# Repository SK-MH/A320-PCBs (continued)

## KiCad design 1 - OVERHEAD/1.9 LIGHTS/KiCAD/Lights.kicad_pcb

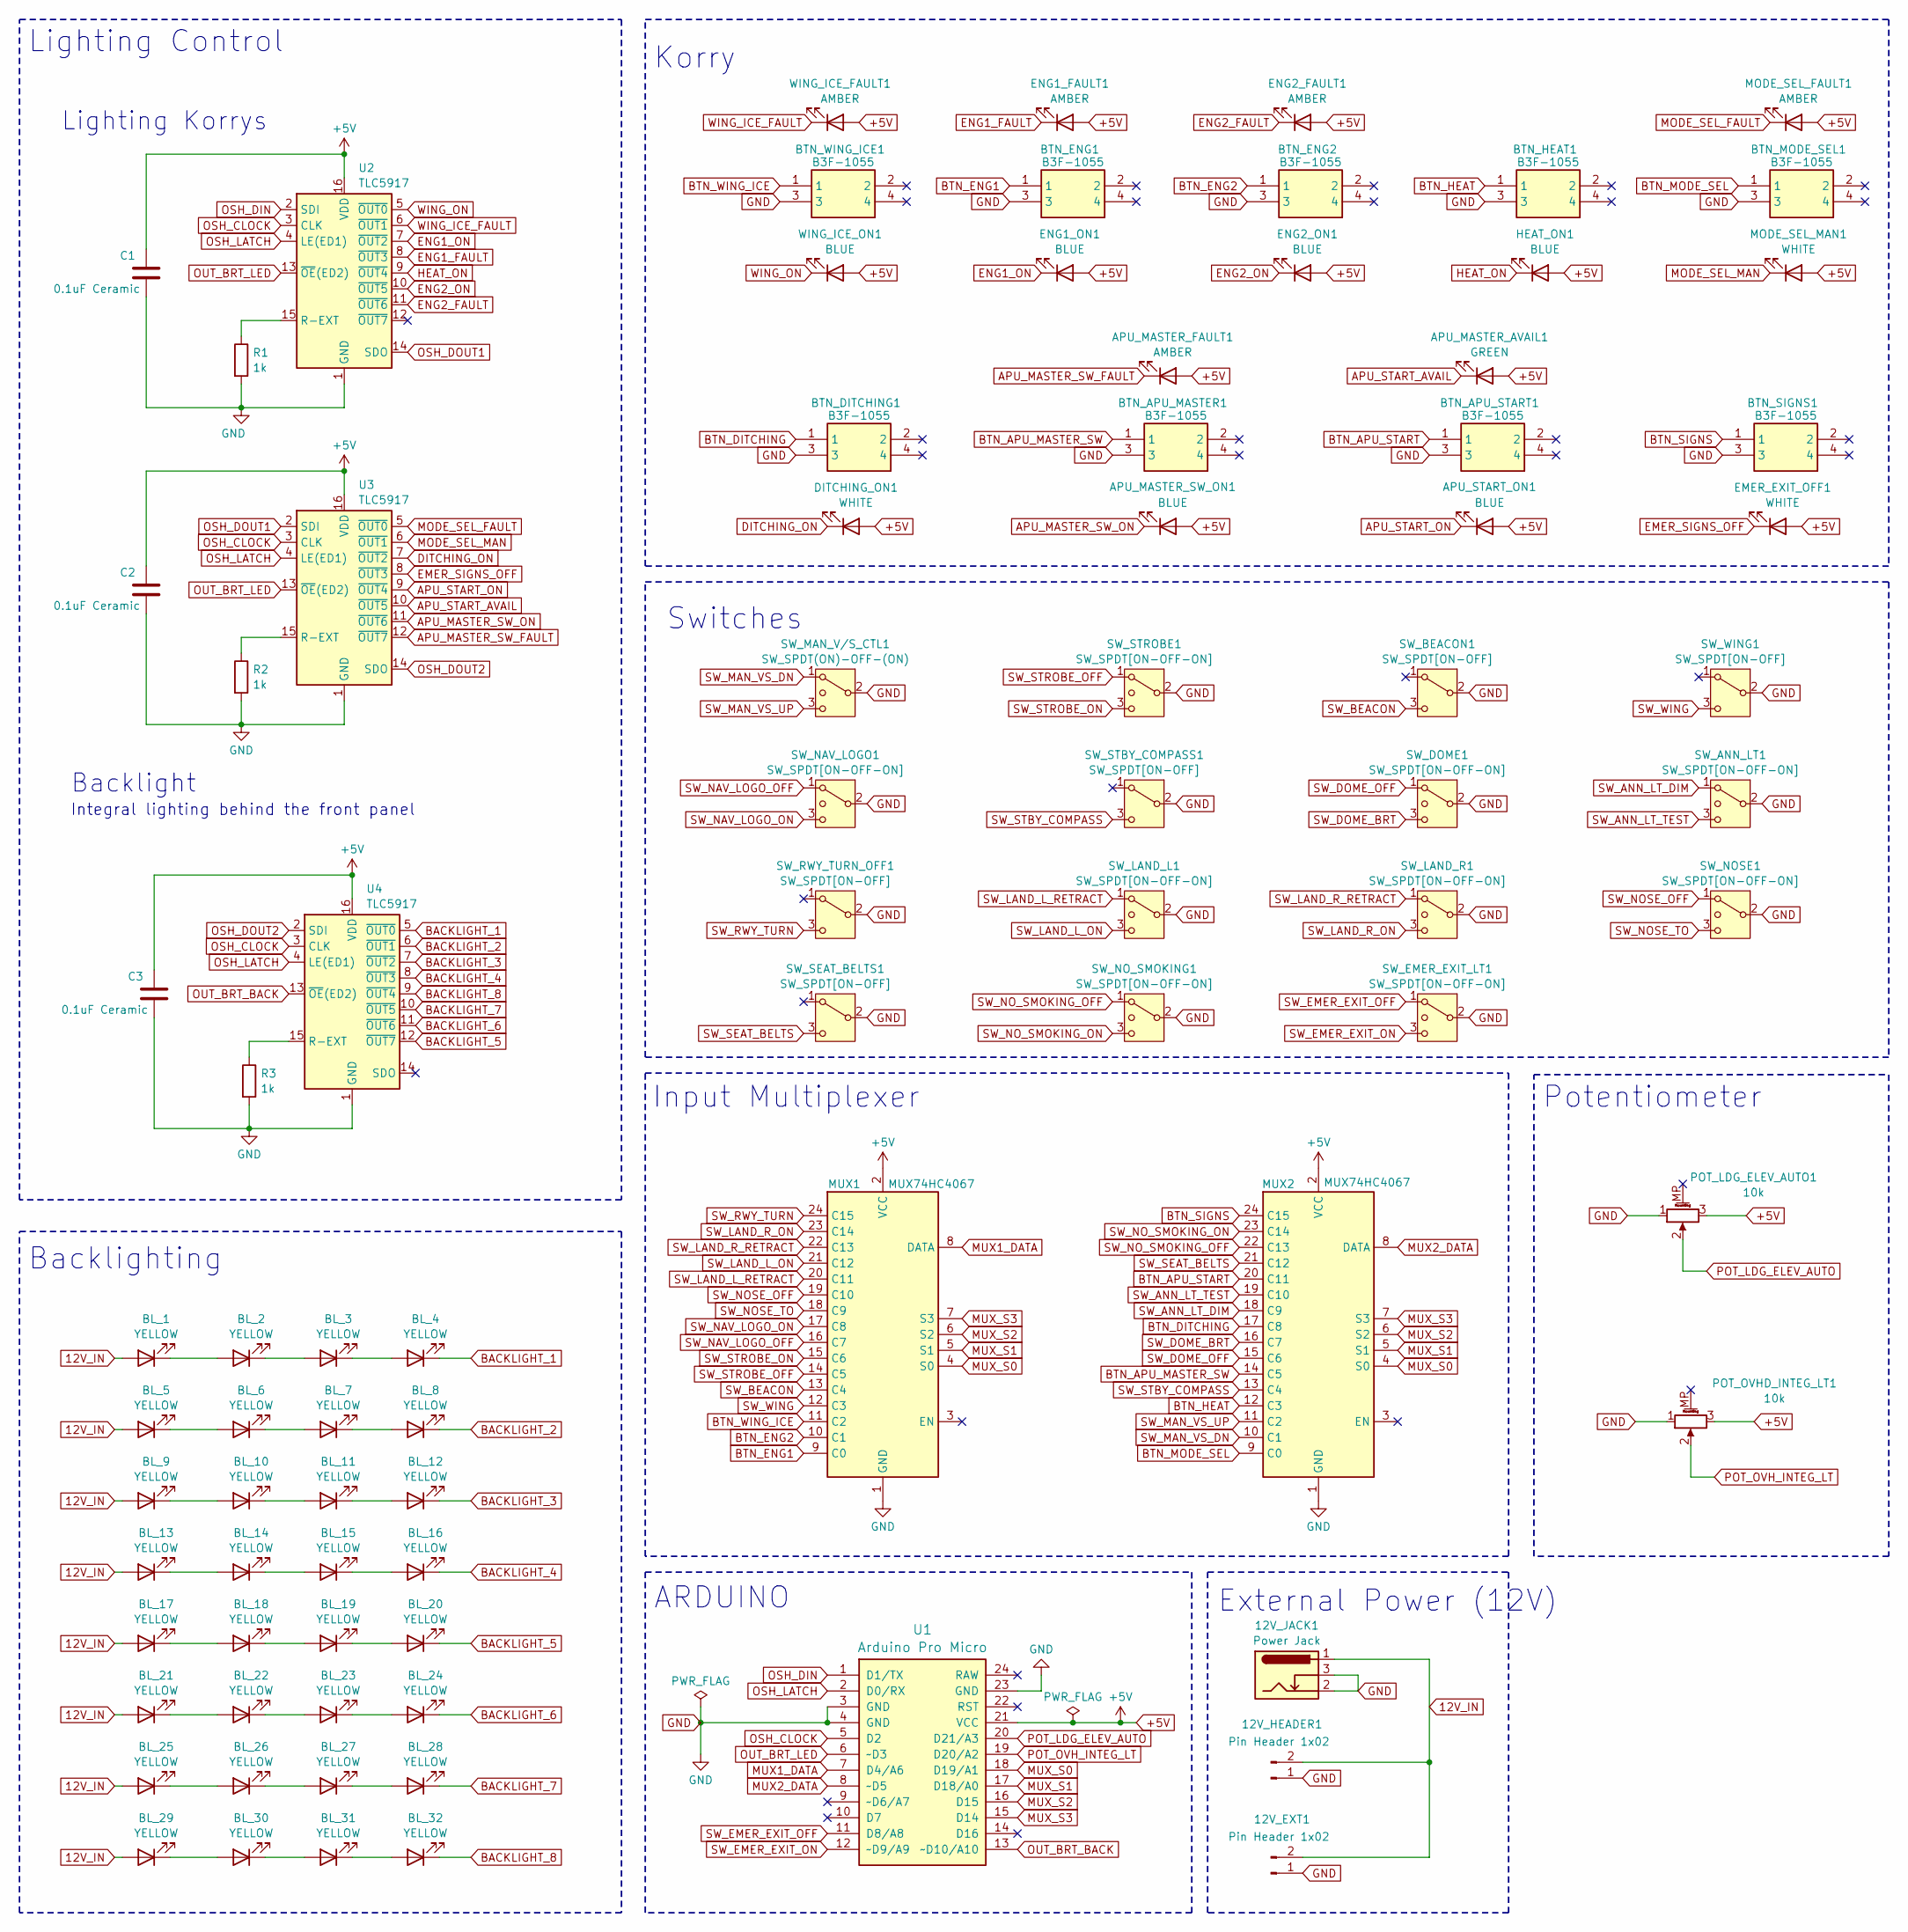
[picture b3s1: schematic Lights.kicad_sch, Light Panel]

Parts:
12V_EXT1, 12V_HEADER1: Pin Header 1x02; JST_EH_B2B-EH-A_1x02_P2.50mm_Vertical
12V_JACK1: Power Jack; BarrelJack_Horizontal
APU_MASTER_AVAIL1: GREEN; LED_D3.0mm
APU_MASTER_FAULT1: AMBER; LED_D3.0mm
APU_MASTER_SW_ON1: BLUE; LED_D3.0mm
APU_START_ON1: BLUE; LED_D3.0mm
BL_1, BL_2, BL_3, BL_4, BL_5, BL_6, BL_7, BL_8, BL_9, BL_10, BL_11, BL_12, BL_13, BL_14, BL_15, BL_16, BL_17, BL_18, BL_19, BL_20, BL_21, BL_22, BL_23, BL_24, BL_25, BL_26, BL_27, BL_28, BL_29, BL_30, BL_31, BL_32: YELLOW; LED_D3.0mm
BTN_APU_MASTER1: B3F-1055; B3F1000; Mouser Part Number 653-B3F-1055
BTN_APU_START1: B3F-1055; B3F1000; Mouser Part Number 653-B3F-1055
BTN_DITCHING1: B3F-1055; B3F1000; Mouser Part Number 653-B3F-1055
BTN_ENG1, BTN_ENG2: B3F-1055; B3F1000; Mouser Part Number 653-B3F-1055
BTN_HEAT1: B3F-1055; B3F1000; Mouser Part Number 653-B3F-1055
BTN_MODE_SEL1: B3F-1055; B3F1000; Mouser Part Number 653-B3F-1055
BTN_SIGNS1: B3F-1055; B3F1000; Mouser Part Number 653-B3F-1055
BTN_WING_ICE1: B3F-1055; B3F1000; Mouser Part Number 653-B3F-1055
C1, C2, C3: 0.1uF Ceramic; C_Disc_D3.0mm_W1.6mm_P2.50mm
DITCHING_ON1: WHITE; LED_D3.0mm
EMER_EXIT_OFF1: WHITE; LED_D3.0mm
ENG1_FAULT1, ENG2_FAULT1: AMBER; LED_D3.0mm
ENG1_ON1, ENG2_ON1: BLUE; LED_D3.0mm
HEAT_ON1: BLUE; LED_D3.0mm
MODE_SEL_FAULT1: AMBER; LED_D3.0mm
MODE_SEL_MAN1: WHITE; LED_D3.0mm
MUX1, MUX2: MUX74HC4067
POT_LDG_ELEV_AUTO1: 10k; Potentiometer_Alps_RK09K_Single_Vertical
POT_OVHD_INTEG_LT1: 10k; Potentiometer_Alps_RK09K_Single_Vertical
R1, R2, R3: 1k; R_Axial_DIN0204_L3.6mm_D1.6mm_P5.08mm_Horizontal
SW_ANN_LT1: SW_SPDT[ON-OFF-ON]; T80-Z1
SW_BEACON1: SW_SPDT[ON-OFF]; T80-Z1
SW_DOME1: SW_SPDT[ON-OFF-ON]; T80-Z1
SW_EMER_EXIT_LT1: SW_SPDT[ON-OFF-ON]; T80-Z1
SW_LAND_L1: SW_SPDT[ON-OFF-ON]; T80-Z1
SW_LAND_R1: SW_SPDT[ON-OFF-ON]; T80-Z1
SW_MAN_V/S_CTL1: SW_SPDT(ON)-OFF-(ON); T80-Z1
SW_NAV_LOGO1: SW_SPDT[ON-OFF-ON]; T80-Z1
SW_NOSE1: SW_SPDT[ON-OFF-ON]; T80-Z1
SW_NO_SMOKING1: SW_SPDT[ON-OFF-ON]; T80-Z1
SW_RWY_TURN_OFF1: SW_SPDT[ON-OFF]; T80-Z1
SW_SEAT_BELTS1: SW_SPDT[ON-OFF]; T80-Z1
SW_STBY_COMPASS1: SW_SPDT[ON-OFF]; T80-Z1
SW_STROBE1: SW_SPDT[ON-OFF-ON]; T80-Z1
SW_WING1: SW_SPDT[ON-OFF]; T80-Z1
U1: Arduino Pro Micro; Sparkfun_Pro_Micro
U2, U3, U4: TLC5917; DIP-16_W7.62mm
WING_ICE_FAULT1: AMBER; LED_D3.0mm
WING_ICE_ON1: BLUE; LED_D3.0mm

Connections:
12V_IN: 12V_EXT1.2, 12V_HEADER1.2, 12V_JACK1.1, BL_1.2 (A), BL_5.2 (A), BL_9.2 (A), BL_13.2 (A), BL_17.2 (A), BL_21.2 (A), BL_25.2 (A), BL_29.2 (A)
+5V: APU_MASTER_AVAIL1.2 (A), APU_MASTER_FAULT1.2 (A), APU_MASTER_SW_ON1.2 (A), APU_START_ON1.2 (A), C1.1, C2.1, C3.1, DITCHING_ON1.2 (A), EMER_EXIT_OFF1.2 (A), ENG1_FAULT1.2 (A), ENG1_ON1.2 (A), ENG2_FAULT1.2 (A), ENG2_ON1.2 (A), HEAT_ON1.2 (A), MODE_SEL_FAULT1.2 (A), MODE_SEL_MAN1.2 (A), MUX1.2 (VCC), MUX2.2 (VCC), POT_LDG_ELEV_AUTO1.3, POT_OVHD_INTEG_LT1.3, U1.21 (VCC), U2.16 (VDD), U3.16 (VDD), U4.16 (VDD), WING_ICE_FAULT1.2 (A), WING_ICE_ON1.2 (A)
APU_MASTER_SW_FAULT: APU_MASTER_FAULT1.1 (K), U3.12 (~OUT7)
APU_MASTER_SW_ON: APU_MASTER_SW_ON1.1 (K), U3.11 (~OUT6)
APU_START_AVAIL: APU_MASTER_AVAIL1.1 (K), U3.10 (~OUT5)
APU_START_ON: APU_START_ON1.1 (K), U3.9 (~OUT4)
BACKLIGHT_1: BL_4.1 (K), U4.5 (~OUT0)
BACKLIGHT_2: BL_8.1 (K), U4.6 (~OUT1)
BACKLIGHT_3: BL_12.1 (K), U4.7 (~OUT2)
BACKLIGHT_4: BL_16.1 (K), U4.8 (~OUT3)
BACKLIGHT_5: BL_20.1 (K), U4.12 (~OUT7)
BACKLIGHT_6: BL_24.1 (K), U4.11 (~OUT6)
BACKLIGHT_7: BL_28.1 (K), U4.10 (~OUT5)
BACKLIGHT_8: BL_32.1 (K), U4.9 (~OUT4)
BTN_APU_MASTER_SW: BTN_APU_MASTER1.1, MUX2.14 (C5)
BTN_APU_START: BTN_APU_START1.1, MUX2.20 (C11)
BTN_DITCHING: BTN_DITCHING1.1, MUX2.17 (C8)
BTN_ENG1: BTN_ENG1.1, MUX1.9 (C0)
BTN_ENG2: BTN_ENG2.1, MUX1.10 (C1)
BTN_HEAT: BTN_HEAT1.1, MUX2.12 (C3)
BTN_MODE_SEL: BTN_MODE_SEL1.1, MUX2.9 (C0)
BTN_SIGNS: BTN_SIGNS1.1, MUX2.24 (C15)
BTN_WING_ICE: BTN_WING_ICE1.1, MUX1.11 (C2)
DITCHING_ON: DITCHING_ON1.1 (K), U3.7 (~OUT2)
EMER_SIGNS_OFF: EMER_EXIT_OFF1.1 (K), U3.8 (~OUT3)
ENG1_FAULT: ENG1_FAULT1.1 (K), U2.8 (~OUT3)
ENG1_ON: ENG1_ON1.1 (K), U2.7 (~OUT2)
ENG2_FAULT: ENG2_FAULT1.1 (K), U2.11 (~OUT6)
ENG2_ON: ENG2_ON1.1 (K), U2.10 (~OUT5)
GND: 12V_EXT1.1, 12V_HEADER1.1, 12V_JACK1.2, 12V_JACK1.3, BTN_APU_MASTER1.3, BTN_APU_START1.3, BTN_DITCHING1.3, BTN_ENG1.3, BTN_ENG2.3, BTN_HEAT1.3, BTN_MODE_SEL1.3, BTN_SIGNS1.3, BTN_WING_ICE1.3, C1.2, C2.2, C3.2, MUX1.1 (GND), MUX2.1 (GND), POT_LDG_ELEV_AUTO1.1, POT_OVHD_INTEG_LT1.1, R1.2, R2.2, R3.2, SW_ANN_LT1.2 (3), SW_BEACON1.2 (B), SW_DOME1.2 (3), SW_EMER_EXIT_LT1.2 (3), SW_LAND_L1.2 (3), SW_LAND_R1.2 (3), SW_MAN_V/S_CTL1.2 (3), SW_NAV_LOGO1.2 (3), SW_NOSE1.2 (3), SW_NO_SMOKING1.2 (3), SW_RWY_TURN_OFF1.2 (B), SW_SEAT_BELTS1.2 (B), SW_STBY_COMPASS1.2 (B), SW_STROBE1.2 (3), SW_WING1.2 (B), U1.3 (GND), U1.4 (GND), U1.23 (GND), U2.1 (GND), U3.1 (GND), U4.1 (GND)
HEAT_ON: HEAT_ON1.1 (K), U2.9 (~OUT4)
MODE_SEL_FAULT: MODE_SEL_FAULT1.1 (K), U3.5 (~OUT0)
MODE_SEL_MAN: MODE_SEL_MAN1.1 (K), U3.6 (~OUT1)
MUX1_DATA: MUX1.8 (DATA), U1.7 (D4/A6)
MUX2_DATA: MUX2.8 (DATA), U1.8 (~D5)
MUX_S0: MUX1.4 (S0), MUX2.4 (S0), U1.18 (D19/A1)
MUX_S1: MUX1.5 (S1), MUX2.5 (S1), U1.17 (D18/A0)
MUX_S2: MUX1.6 (S2), MUX2.6 (S2), U1.16 (D15)
MUX_S3: MUX1.7 (S3), MUX2.7 (S3), U1.15 (D14)
unnamed: BL_1.1 (K), BL_2.2 (A)
unnamed: BL_2.1 (K), BL_3.2 (A)
unnamed: BL_3.1 (K), BL_4.2 (A)
unnamed: BL_5.1 (K), BL_6.2 (A)
unnamed: BL_6.1 (K), BL_7.2 (A)
unnamed: BL_7.1 (K), BL_8.2 (A)
unnamed: BL_9.1 (K), BL_10.2 (A)
unnamed: BL_10.1 (K), BL_11.2 (A)
unnamed: BL_11.1 (K), BL_12.2 (A)
unnamed: BL_13.1 (K), BL_14.2 (A)
unnamed: BL_14.1 (K), BL_15.2 (A)
unnamed: BL_15.1 (K), BL_16.2 (A)
unnamed: BL_17.1 (K), BL_18.2 (A)
unnamed: BL_18.1 (K), BL_19.2 (A)
unnamed: BL_19.1 (K), BL_20.2 (A)
unnamed: BL_21.1 (K), BL_22.2 (A)
unnamed: BL_22.1 (K), BL_23.2 (A)
unnamed: BL_23.1 (K), BL_24.2 (A)
unnamed: BL_25.1 (K), BL_26.2 (A)
unnamed: BL_26.1 (K), BL_27.2 (A)
unnamed: BL_27.1 (K), BL_28.2 (A)
unnamed: BL_29.1 (K), BL_30.2 (A)
unnamed: BL_30.1 (K), BL_31.2 (A)
unnamed: BL_31.1 (K), BL_32.2 (A)
unnamed: R1.1, U2.15 (R-EXT)
unnamed: R2.1, U3.15 (R-EXT)
unnamed: R3.1, U4.15 (R-EXT)
OSH_CLOCK: U1.5 (D2), U2.3 (CLK), U3.3 (CLK), U4.3 (CLK)
OSH_DIN: U1.1 (D1/TX), U2.2 (SDI)
OSH_DOUT1: U2.14 (SDO), U3.2 (SDI)
OSH_DOUT2: U3.14 (SDO), U4.2 (SDI)
OSH_LATCH: U1.2 (D0/RX), U2.4 (LE(ED1)), U3.4 (LE(ED1)), U4.4 (LE(ED1))
OUT_BRT_BACK: U1.13 (~D10/A10), U4.13 (~OE(ED2))
OUT_BRT_LED: U1.6 (~D3), U2.13 (~OE(ED2)), U3.13 (~OE(ED2))
POT_LDG_ELEV_AUTO: POT_LDG_ELEV_AUTO1.2, U1.20 (D21/A3)
POT_OVH_INTEG_LT: POT_OVHD_INTEG_LT1.2, U1.19 (D20/A2)
SW_ANN_LT_DIM: MUX2.18 (C9), SW_ANN_LT1.1
SW_ANN_LT_TEST: MUX2.19 (C10), SW_ANN_LT1.3 (4)
SW_BEACON: MUX1.13 (C4), SW_BEACON1.3 (C)
SW_DOME_BRT: MUX2.16 (C7), SW_DOME1.3 (4)
SW_DOME_OFF: MUX2.15 (C6), SW_DOME1.1
SW_EMER_EXIT_OFF: SW_EMER_EXIT_LT1.1, U1.11 (D8/A8)
SW_EMER_EXIT_ON: SW_EMER_EXIT_LT1.3 (4), U1.12 (~D9/A9)
SW_LAND_L_ON: MUX1.21 (C12), SW_LAND_L1.3 (4)
SW_LAND_L_RETRACT: MUX1.20 (C11), SW_LAND_L1.1
SW_LAND_R_ON: MUX1.23 (C14), SW_LAND_R1.3 (4)
SW_LAND_R_RETRACT: MUX1.22 (C13), SW_LAND_R1.1
SW_MAN_VS_DN: MUX2.10 (C1), SW_MAN_V/S_CTL1.1
SW_MAN_VS_UP: MUX2.11 (C2), SW_MAN_V/S_CTL1.3 (4)
SW_NAV_LOGO_OFF: MUX1.16 (C7), SW_NAV_LOGO1.1
SW_NAV_LOGO_ON: MUX1.17 (C8), SW_NAV_LOGO1.3 (4)
SW_NOSE_OFF: MUX1.19 (C10), SW_NOSE1.1
SW_NOSE_TO: MUX1.18 (C9), SW_NOSE1.3 (4)
SW_NO_SMOKING_OFF: MUX2.22 (C13), SW_NO_SMOKING1.1
SW_NO_SMOKING_ON: MUX2.23 (C14), SW_NO_SMOKING1.3 (4)
SW_RWY_TURN: MUX1.24 (C15), SW_RWY_TURN_OFF1.3 (C)
SW_SEAT_BELTS: MUX2.21 (C12), SW_SEAT_BELTS1.3 (C)
SW_STBY_COMPASS: MUX2.13 (C4), SW_STBY_COMPASS1.3 (C)
SW_STROBE_OFF: MUX1.14 (C5), SW_STROBE1.1
SW_STROBE_ON: MUX1.15 (C6), SW_STROBE1.3 (4)
SW_WING: MUX1.12 (C3), SW_WING1.3 (C)
WING_ICE_FAULT: U2.6 (~OUT1), WING_ICE_FAULT1.1 (K)
WING_ON: U2.5 (~OUT0), WING_ICE_ON1.1 (K)

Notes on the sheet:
Backlighting
ARDUINO
Switches
Korry
Potentiometer
Input Multiplexer
External Power (12V)
Lighting Korrys
Lighting Control
Integral lighting behind the front panel
Backlight

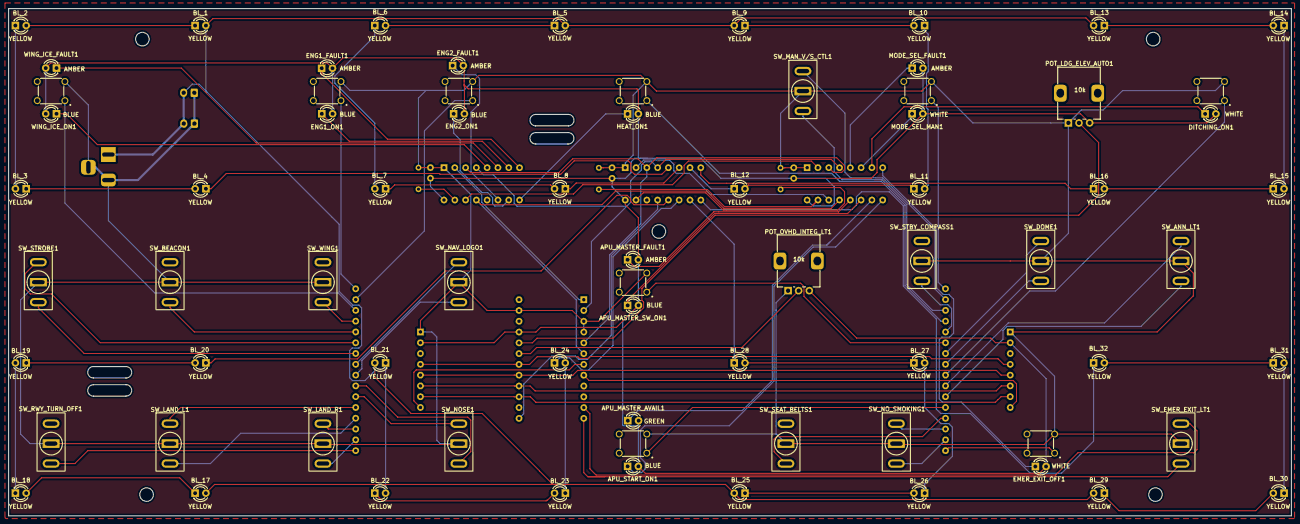
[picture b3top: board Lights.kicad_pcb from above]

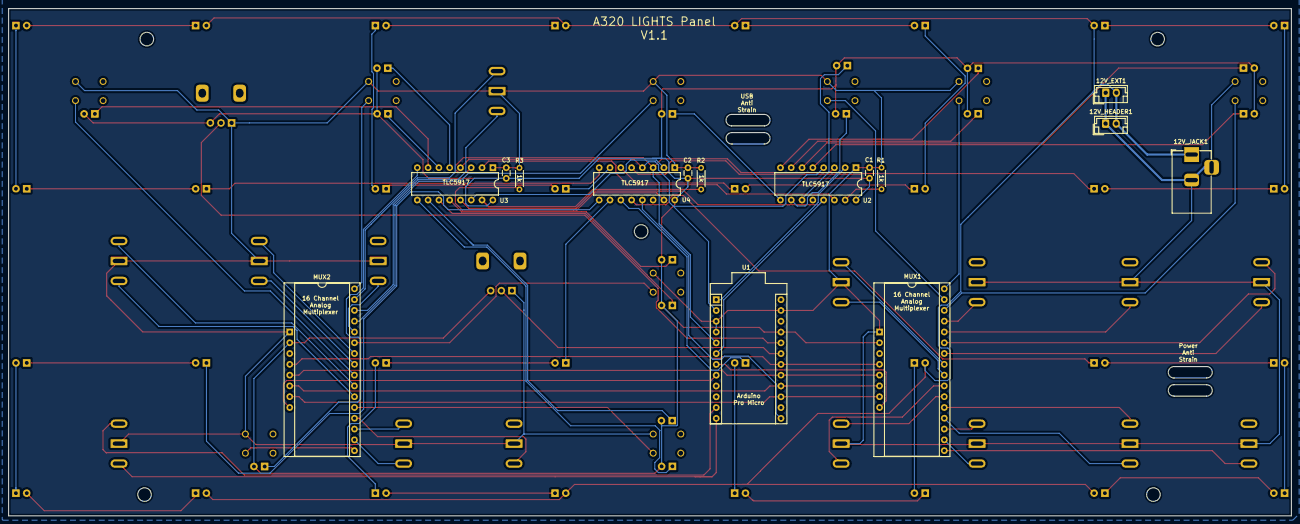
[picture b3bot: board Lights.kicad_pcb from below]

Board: 2 copper layers, 302.0 x 119.4 mm, 88 parts (15 on the bottom side), 102 nets.

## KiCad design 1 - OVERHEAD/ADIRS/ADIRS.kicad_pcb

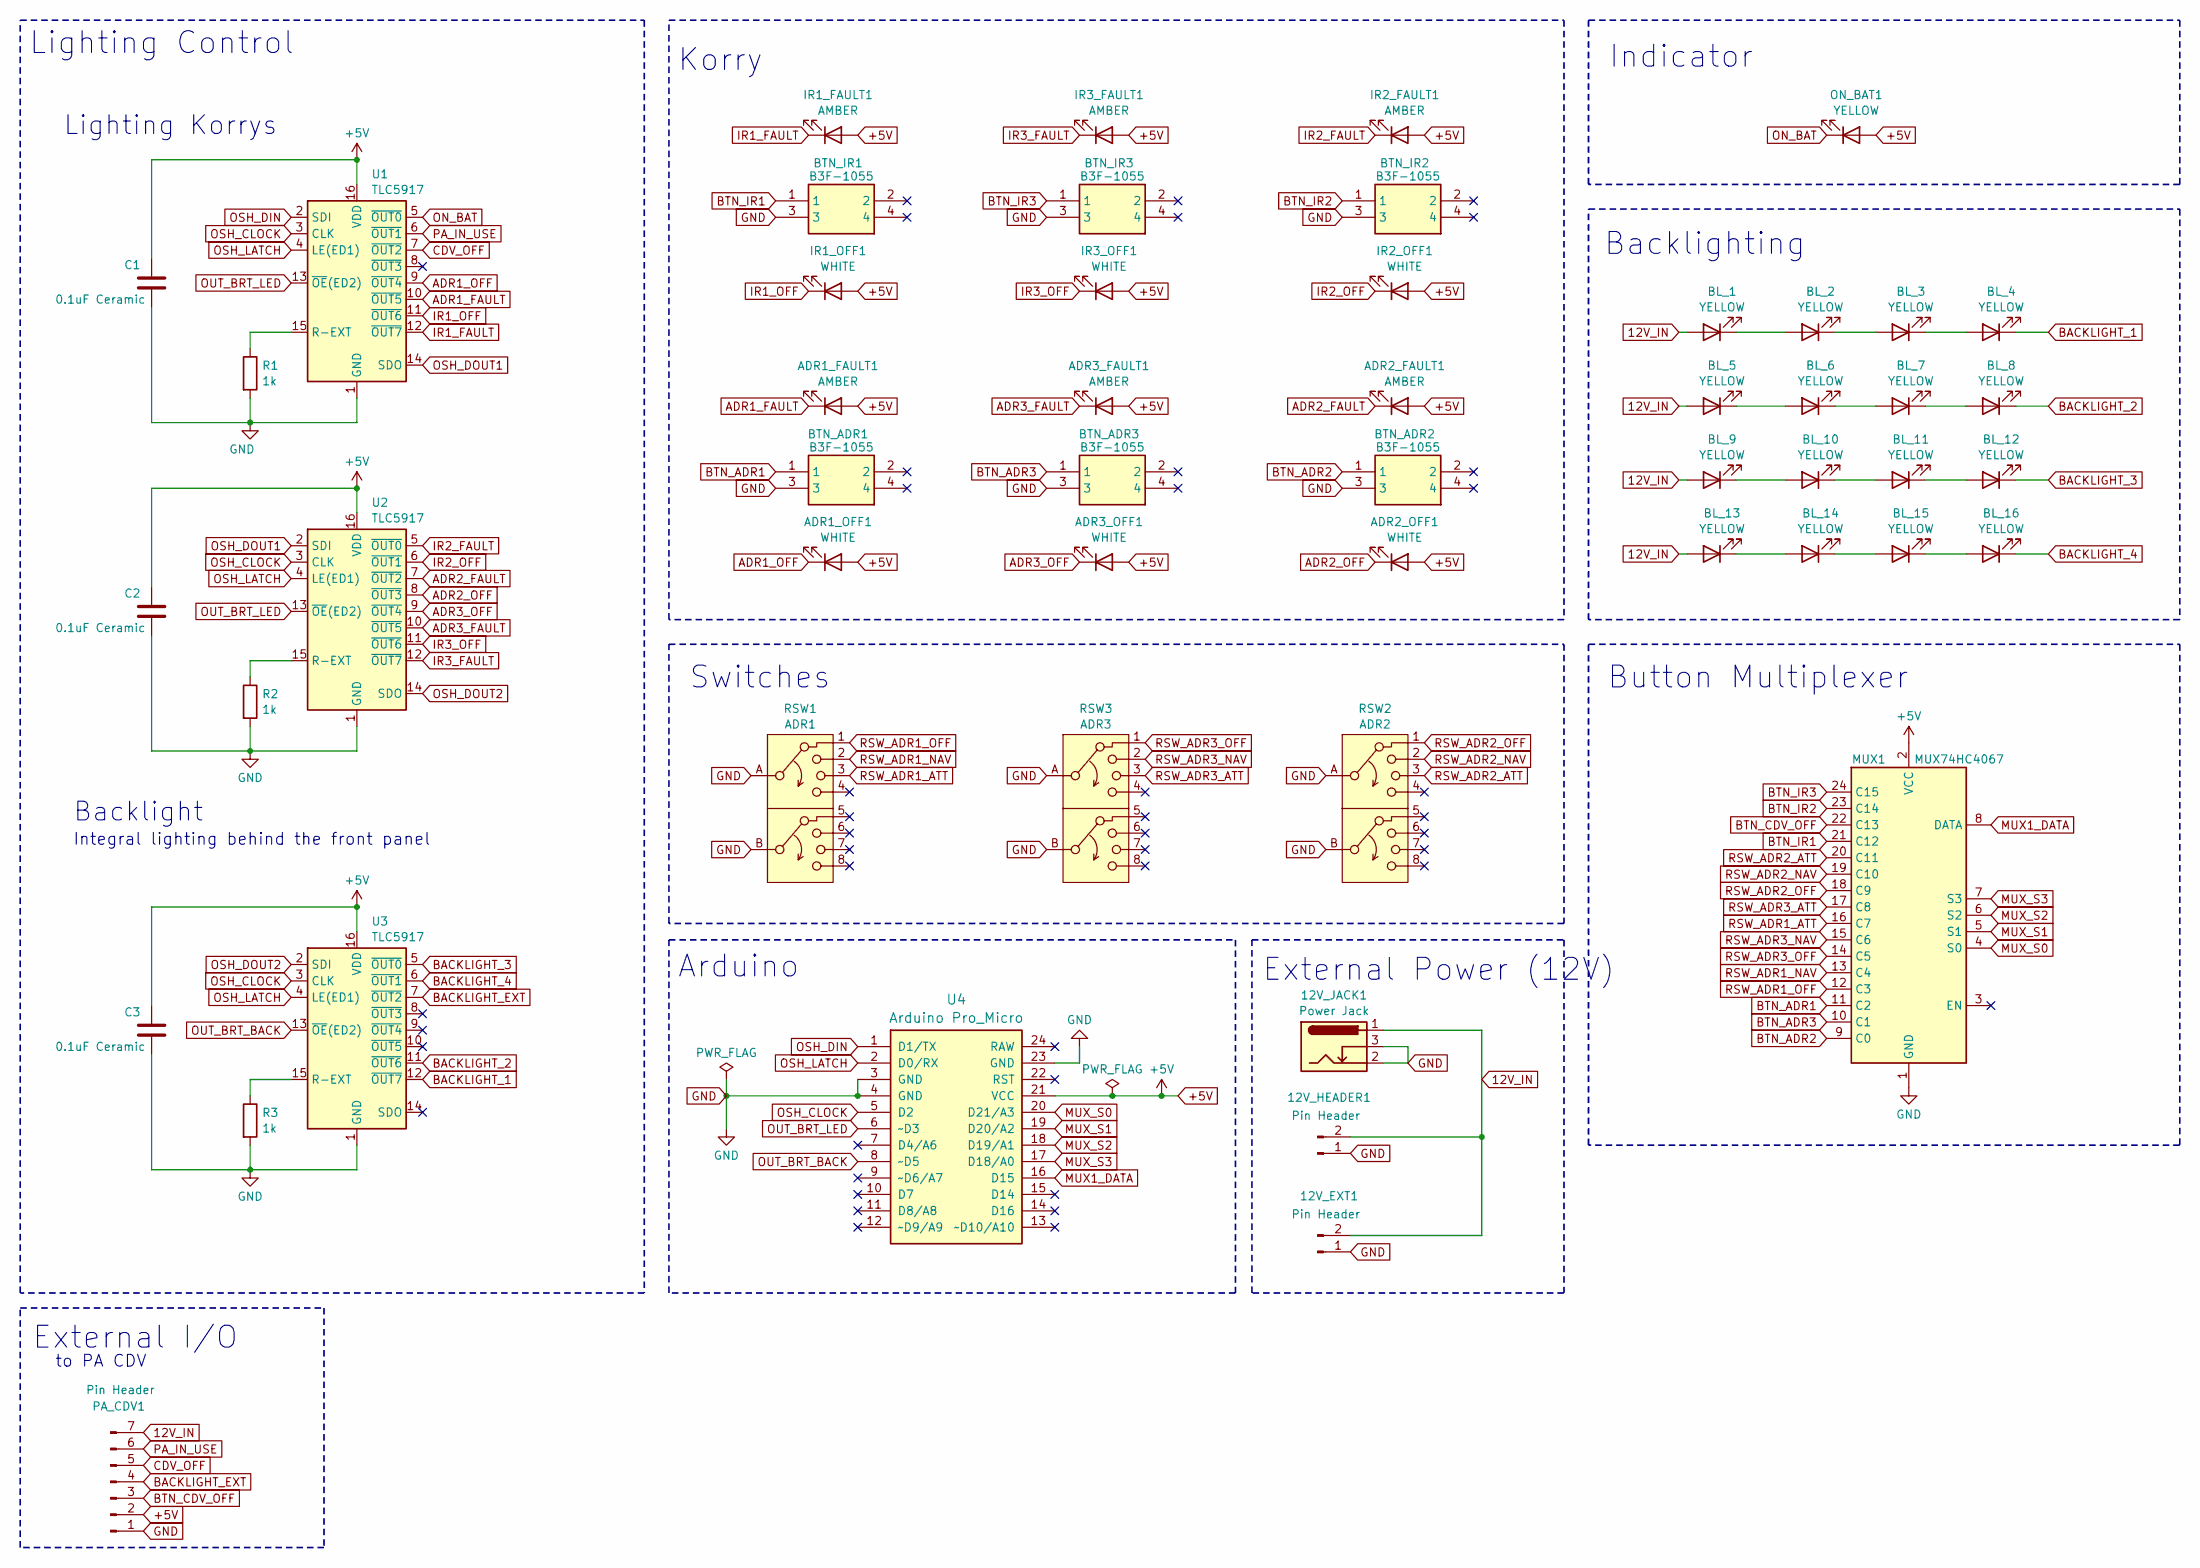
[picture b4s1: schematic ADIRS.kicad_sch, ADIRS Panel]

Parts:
12V_EXT1, 12V_HEADER1: Pin Header; JST_EH_B2B-EH-A_1x02_P2.50mm_Vertical
12V_JACK1: Power Jack; BarrelJack_Horizontal
ADR1_FAULT1, ADR2_FAULT1, ADR3_FAULT1: AMBER; LED_D3.0mm
ADR1_OFF1, ADR2_OFF1, ADR3_OFF1: WHITE; LED_D3.0mm
BL_1, BL_2, BL_3, BL_4, BL_5, BL_6, BL_7, BL_8, BL_9, BL_10, BL_11, BL_12, BL_13, BL_14, BL_15, BL_16: YELLOW; LED_D3.0mm
BTN_ADR1, BTN_ADR2, BTN_ADR3: B3F-1055; B3F1000; Mouser Part Number 653-B3F-1055
BTN_IR1, BTN_IR2, BTN_IR3: B3F-1055; B3F1000; Mouser Part Number 653-B3F-1055
C1, C2, C3: 0.1uF Ceramic; C_Disc_D3.0mm_W1.6mm_P2.50mm
IR1_FAULT1, IR2_FAULT1, IR3_FAULT1: AMBER; LED_D3.0mm
IR1_OFF1, IR2_OFF1, IR3_OFF1: WHITE; LED_D3.0mm
MUX1: MUX74HC4067
ON_BAT1: YELLOW; LED_D3.0mm
PA_CDV1: Pin Header; JST_EH_B7B-EH-A_1x07_P2.50mm_Vertical
R1, R2, R3: 1k; R_Axial_DIN0204_L3.6mm_D1.6mm_P7.62mm_Horizontal
RSW1: ADR1; SR16-AB
RSW2: ADR2; SR16-AB
RSW3: ADR3; SR16-AB
U1, U2, U3: TLC5917; DIP-16_W7.62mm
U4: Arduino Pro_Micro; Sparkfun_Pro_Micro

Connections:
12V_IN: 12V_EXT1.2, 12V_HEADER1.2, 12V_JACK1.1, BL_1.2 (A), BL_5.2 (A), BL_9.2 (A), BL_13.2 (A), PA_CDV1.7
+5V: ADR1_FAULT1.2 (A), ADR1_OFF1.2 (A), ADR2_FAULT1.2 (A), ADR2_OFF1.2 (A), ADR3_FAULT1.2 (A), ADR3_OFF1.2 (A), C1.1, C2.1, C3.1, IR1_FAULT1.2 (A), IR1_OFF1.2 (A), IR2_FAULT1.2 (A), IR2_OFF1.2 (A), IR3_FAULT1.2 (A), IR3_OFF1.2 (A), MUX1.2 (VCC), ON_BAT1.2 (A), PA_CDV1.2, U1.16 (VDD), U2.16 (VDD), U3.16 (VDD), U4.21 (VCC)
ADR1_FAULT: ADR1_FAULT1.1 (K), U1.10 (~OUT5)
ADR1_OFF: ADR1_OFF1.1 (K), U1.9 (~OUT4)
ADR2_FAULT: ADR2_FAULT1.1 (K), U2.7 (~OUT2)
ADR2_OFF: ADR2_OFF1.1 (K), U2.8 (~OUT3)
ADR3_FAULT: ADR3_FAULT1.1 (K), U2.10 (~OUT5)
ADR3_OFF: ADR3_OFF1.1 (K), U2.9 (~OUT4)
BACKLIGHT_1: BL_4.1 (K), U3.12 (~OUT7)
BACKLIGHT_2: BL_8.1 (K), U3.11 (~OUT6)
BACKLIGHT_3: BL_12.1 (K), U3.5 (~OUT0)
BACKLIGHT_4: BL_16.1 (K), U3.6 (~OUT1)
BACKLIGHT_EXT: PA_CDV1.4, U3.7 (~OUT2)
BTN_ADR1: BTN_ADR1.1, MUX1.11 (C2)
BTN_ADR2: BTN_ADR2.1, MUX1.9 (C0)
BTN_ADR3: BTN_ADR3.1, MUX1.10 (C1)
BTN_CDV_OFF: MUX1.22 (C13), PA_CDV1.3
BTN_IR1: BTN_IR1.1, MUX1.21 (C12)
BTN_IR2: BTN_IR2.1, MUX1.23 (C14)
BTN_IR3: BTN_IR3.1, MUX1.24 (C15)
CDV_OFF: PA_CDV1.5, U1.7 (~OUT2)
GND: 12V_EXT1.1, 12V_HEADER1.1, 12V_JACK1.2, 12V_JACK1.3, BTN_ADR1.3, BTN_ADR2.3, BTN_ADR3.3, BTN_IR1.3, BTN_IR2.3, BTN_IR3.3, C1.2, C2.2, C3.2, MUX1.1 (GND), PA_CDV1.1, R1.2, R2.2, R3.2, RSW1.A, RSW1.B, RSW2.A, RSW2.B, RSW3.A, RSW3.B, U1.1 (GND), U2.1 (GND), U3.1 (GND), U4.3 (GND), U4.4 (GND), U4.23 (GND)
IR1_FAULT: IR1_FAULT1.1 (K), U1.12 (~OUT7)
IR1_OFF: IR1_OFF1.1 (K), U1.11 (~OUT6)
IR2_FAULT: IR2_FAULT1.1 (K), U2.5 (~OUT0)
IR2_OFF: IR2_OFF1.1 (K), U2.6 (~OUT1)
IR3_FAULT: IR3_FAULT1.1 (K), U2.12 (~OUT7)
IR3_OFF: IR3_OFF1.1 (K), U2.11 (~OUT6)
MUX1_DATA: MUX1.8 (DATA), U4.16 (D15)
MUX_S0: MUX1.4 (S0), U4.20 (D21/A3)
MUX_S1: MUX1.5 (S1), U4.19 (D20/A2)
MUX_S2: MUX1.6 (S2), U4.18 (D19/A1)
MUX_S3: MUX1.7 (S3), U4.17 (D18/A0)
unnamed: BL_1.1 (K), BL_2.2 (A)
unnamed: BL_2.1 (K), BL_3.2 (A)
unnamed: BL_3.1 (K), BL_4.2 (A)
unnamed: BL_5.1 (K), BL_6.2 (A)
unnamed: BL_6.1 (K), BL_7.2 (A)
unnamed: BL_7.1 (K), BL_8.2 (A)
unnamed: BL_9.1 (K), BL_10.2 (A)
unnamed: BL_10.1 (K), BL_11.2 (A)
unnamed: BL_11.1 (K), BL_12.2 (A)
unnamed: BL_13.1 (K), BL_14.2 (A)
unnamed: BL_14.1 (K), BL_15.2 (A)
unnamed: BL_15.1 (K), BL_16.2 (A)
unnamed: R1.1, U1.15 (R-EXT)
unnamed: R2.1, U2.15 (R-EXT)
unnamed: R3.1, U3.15 (R-EXT)
ON_BAT: ON_BAT1.1 (K), U1.5 (~OUT0)
OSH_CLOCK: U1.3 (CLK), U2.3 (CLK), U3.3 (CLK), U4.5 (D2)
OSH_DIN: U1.2 (SDI), U4.1 (D1/TX)
OSH_DOUT1: U1.14 (SDO), U2.2 (SDI)
OSH_DOUT2: U2.14 (SDO), U3.2 (SDI)
OSH_LATCH: U1.4 (LE(ED1)), U2.4 (LE(ED1)), U3.4 (LE(ED1)), U4.2 (D0/RX)
OUT_BRT_BACK: U3.13 (~OE(ED2)), U4.8 (~D5)
OUT_BRT_LED: U1.13 (~OE(ED2)), U2.13 (~OE(ED2)), U4.6 (~D3)
PA_IN_USE: PA_CDV1.6, U1.6 (~OUT1)
RSW_ADR1_ATT: MUX1.16 (C7), RSW1.3
RSW_ADR1_NAV: MUX1.13 (C4), RSW1.2
RSW_ADR1_OFF: MUX1.12 (C3), RSW1.1
RSW_ADR2_ATT: MUX1.20 (C11), RSW2.3
RSW_ADR2_NAV: MUX1.19 (C10), RSW2.2
RSW_ADR2_OFF: MUX1.18 (C9), RSW2.1
RSW_ADR3_ATT: MUX1.17 (C8), RSW3.3
RSW_ADR3_NAV: MUX1.15 (C6), RSW3.2
RSW_ADR3_OFF: MUX1.14 (C5), RSW3.1

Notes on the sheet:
Backlighting
External I/O
Arduino
Switches
Indicator
Korry
Button Multiplexer
to PA CDV
External Power (12V)
Lighting Korrys
Lighting Control
Integral lighting behind the front panel
Backlight

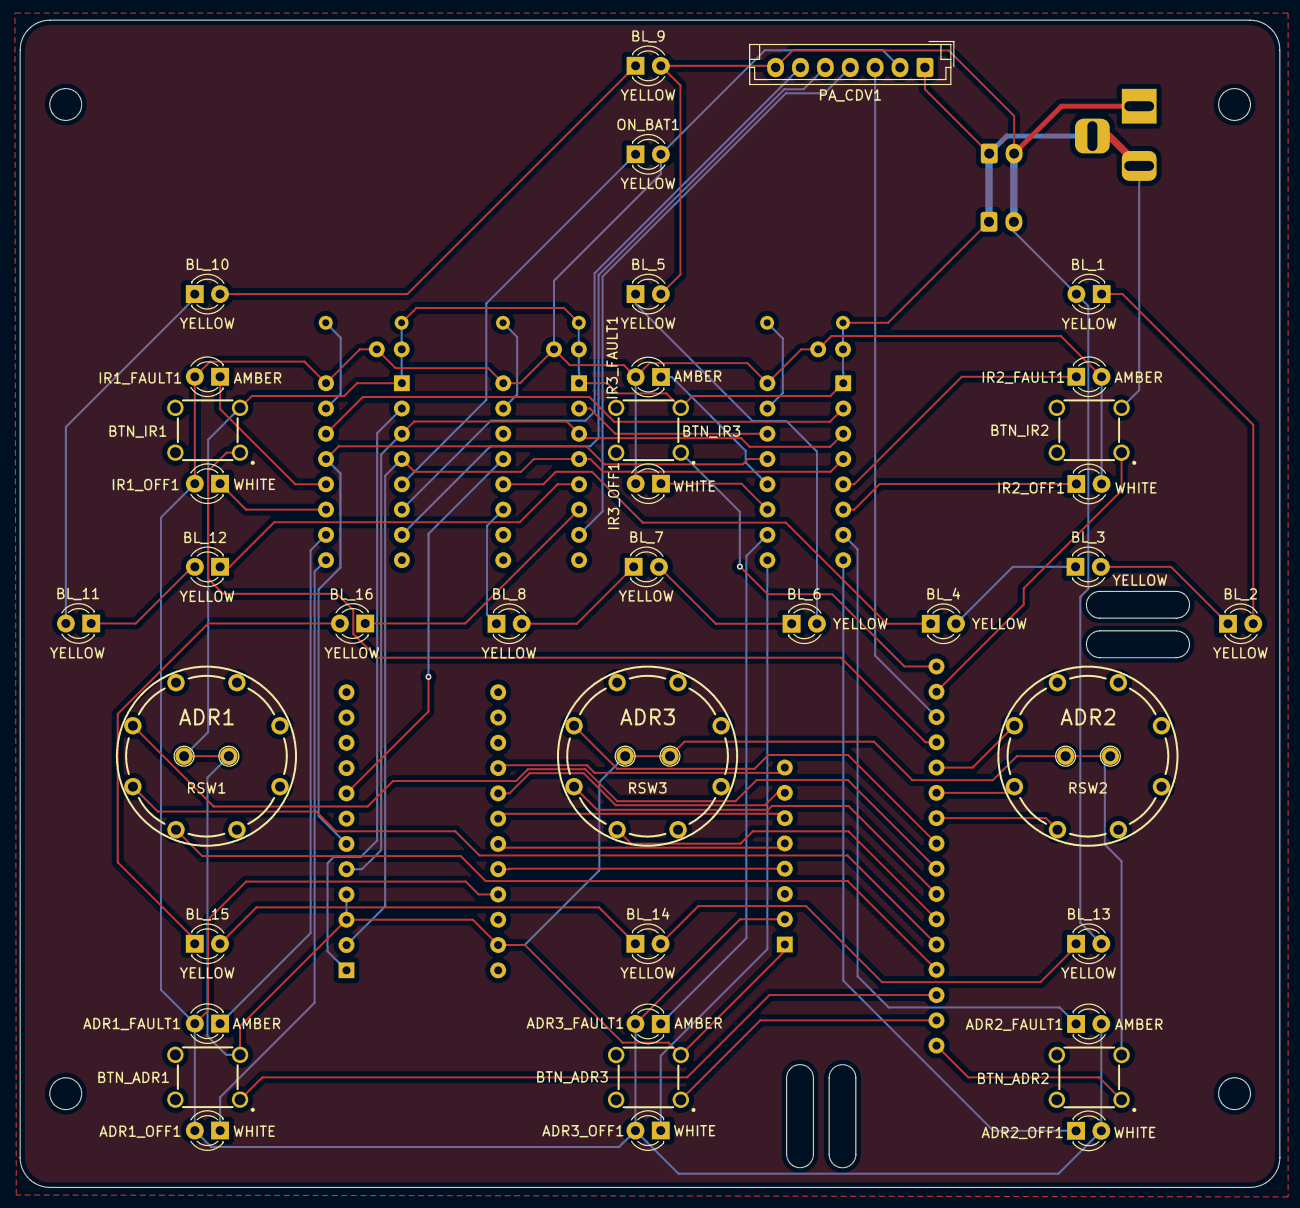
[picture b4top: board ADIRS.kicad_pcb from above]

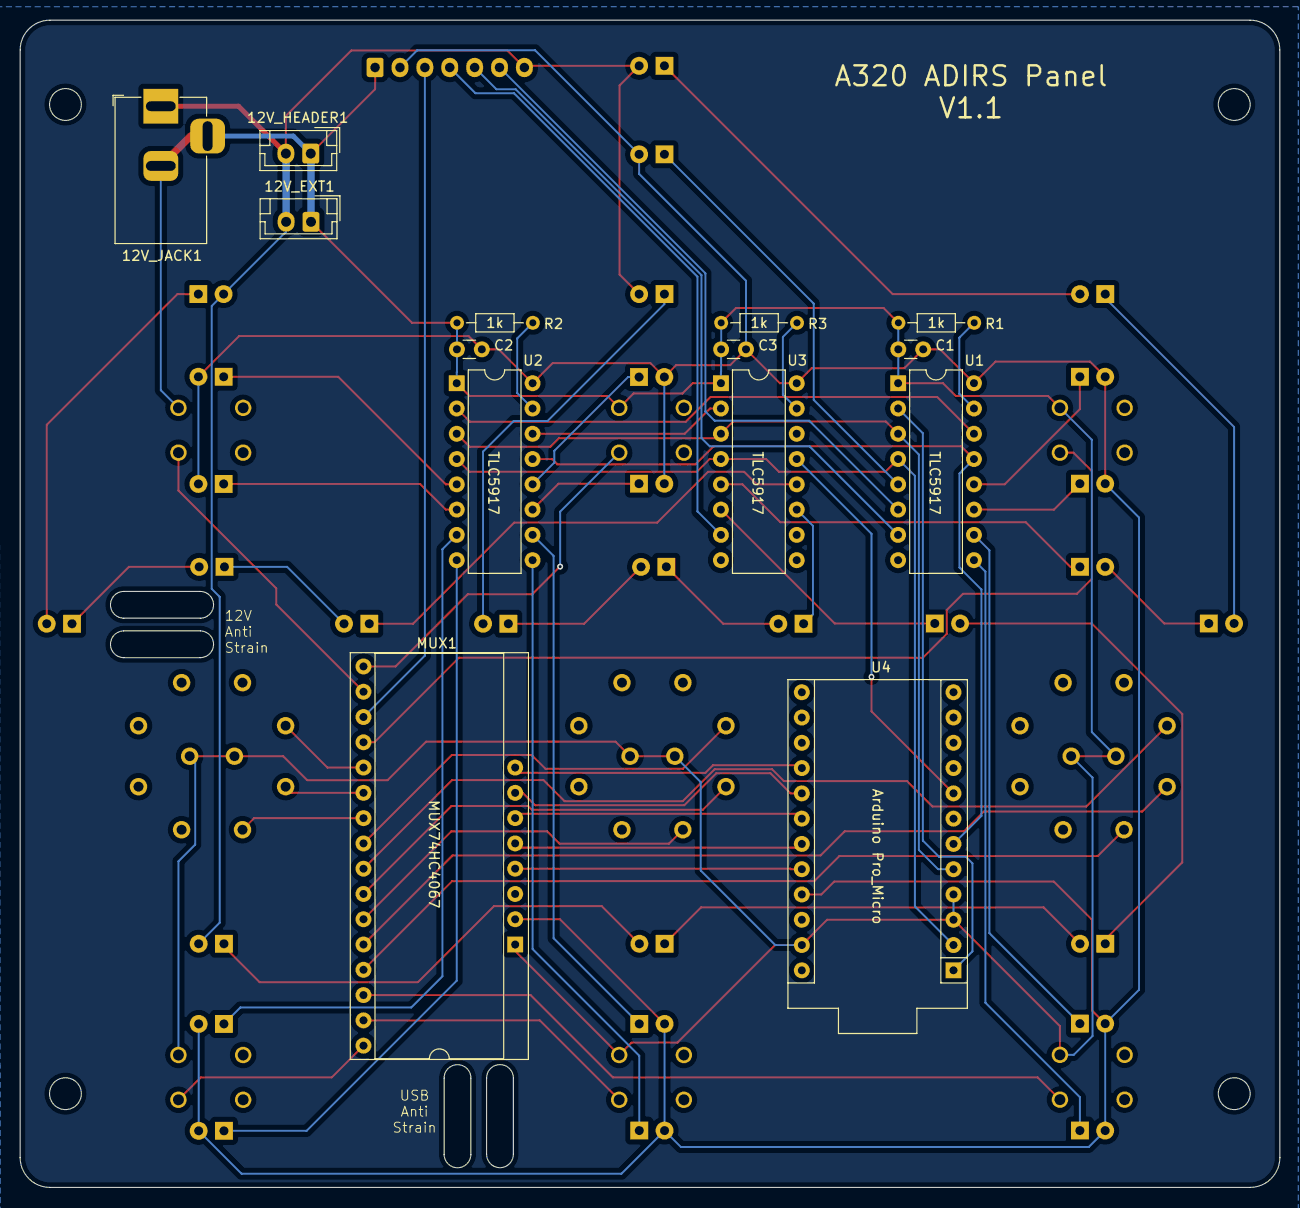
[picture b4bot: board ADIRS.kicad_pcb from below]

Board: 2 copper layers, 126.6 x 117.3 mm, 53 parts (14 on the bottom side), 66 nets.

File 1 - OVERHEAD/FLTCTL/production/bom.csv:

Designator,Footprint,Quantity,Value,LCSC Part #
"BL_1, BL_2, BL_3, BL_4",LED_D3.0mm,4,YELLOW,
"BTN_ELAC1, BTN_FAC1, BTN_SEC1",B3F1000,3,B3F-1055,
"ELAC1_FAULT1, FAC1_FAULT1, SEC1_FAULT1",LED_D3.0mm,3,AMBER,
"ELAC1_OFF1, FAC1_OFF1, SEC1_OFF1",LED_D3.0mm,3,WHITE,
FLT_CTL_CPT1,IDC-Header_2x07_P2.54mm_Vertical,1,Pin Header,

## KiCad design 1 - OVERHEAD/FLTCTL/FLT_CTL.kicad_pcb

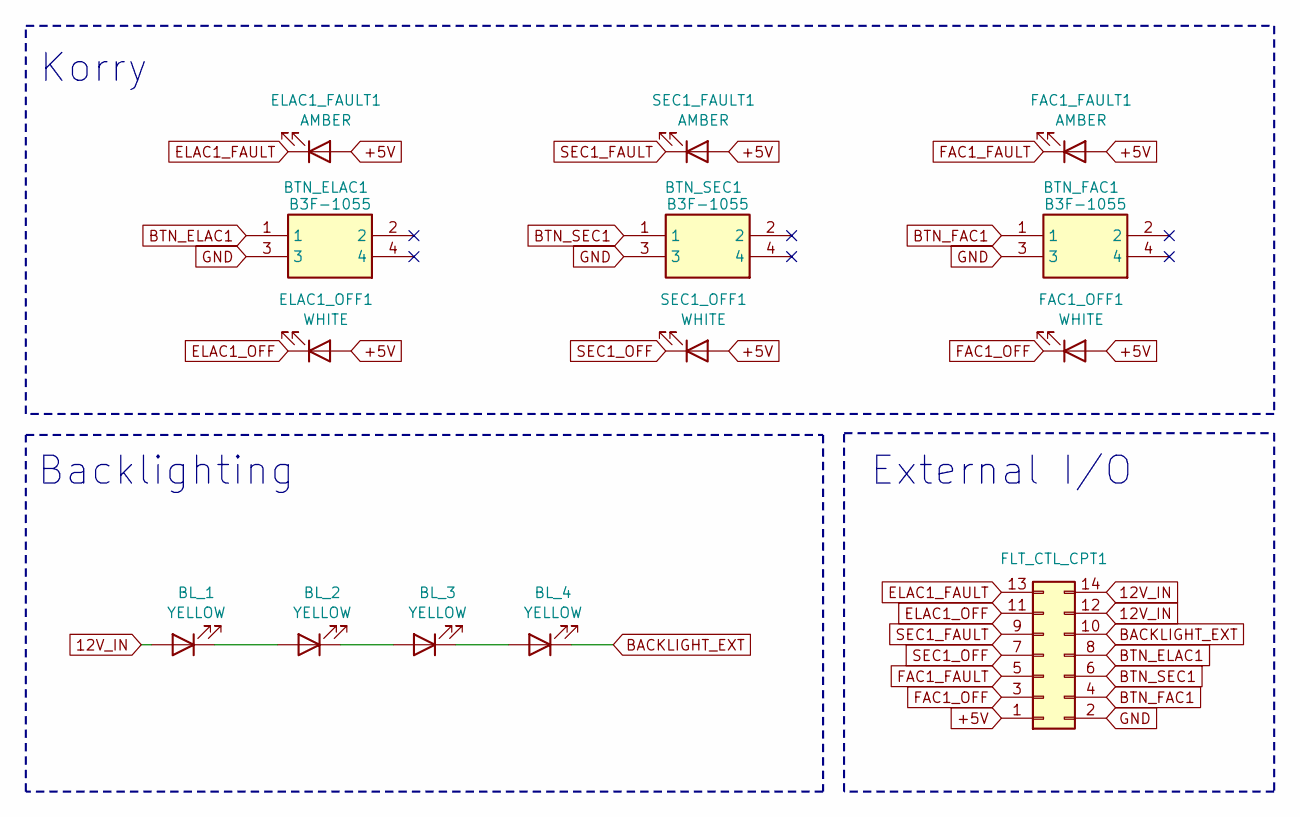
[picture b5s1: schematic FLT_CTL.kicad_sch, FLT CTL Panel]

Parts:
BL_1, BL_2, BL_3, BL_4: YELLOW; LED_D3.0mm
BTN_ELAC1: B3F-1055; B3F1000; Mouser Part Number 653-B3F-1055
BTN_FAC1: B3F-1055; B3F1000; Mouser Part Number 653-B3F-1055
BTN_SEC1: B3F-1055; B3F1000; Mouser Part Number 653-B3F-1055
ELAC1_FAULT1: AMBER; LED_D3.0mm
ELAC1_OFF1: WHITE; LED_D3.0mm
FAC1_FAULT1: AMBER; LED_D3.0mm
FAC1_OFF1: WHITE; LED_D3.0mm
FLT_CTL_CPT1: Pin Header; IDC-Header_2x07_P2.54mm_Vertical
SEC1_FAULT1: AMBER; LED_D3.0mm
SEC1_OFF1: WHITE; LED_D3.0mm

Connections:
12V_IN: BL_1.2 (A), FLT_CTL_CPT1.12, FLT_CTL_CPT1.14
+5V: ELAC1_FAULT1.2 (A), ELAC1_OFF1.2 (A), FAC1_FAULT1.2 (A), FAC1_OFF1.2 (A), FLT_CTL_CPT1.1, SEC1_FAULT1.2 (A), SEC1_OFF1.2 (A)
BACKLIGHT_EXT: BL_4.1 (K), FLT_CTL_CPT1.10
BTN_ELAC1: BTN_ELAC1.1, FLT_CTL_CPT1.8
BTN_FAC1: BTN_FAC1.1, FLT_CTL_CPT1.4
BTN_SEC1: BTN_SEC1.1, FLT_CTL_CPT1.6
ELAC1_FAULT: ELAC1_FAULT1.1 (K), FLT_CTL_CPT1.13
ELAC1_OFF: ELAC1_OFF1.1 (K), FLT_CTL_CPT1.11
FAC1_FAULT: FAC1_FAULT1.1 (K), FLT_CTL_CPT1.5
FAC1_OFF: FAC1_OFF1.1 (K), FLT_CTL_CPT1.3
GND: BTN_ELAC1.3, BTN_FAC1.3, BTN_SEC1.3, FLT_CTL_CPT1.2
unnamed: BL_1.1 (K), BL_2.2 (A)
unnamed: BL_2.1 (K), BL_3.2 (A)
unnamed: BL_3.1 (K), BL_4.2 (A)
SEC1_FAULT: FLT_CTL_CPT1.9, SEC1_FAULT1.1 (K)
SEC1_OFF: FLT_CTL_CPT1.7, SEC1_OFF1.1 (K)

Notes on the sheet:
Backlighting
External I/O
Korry
